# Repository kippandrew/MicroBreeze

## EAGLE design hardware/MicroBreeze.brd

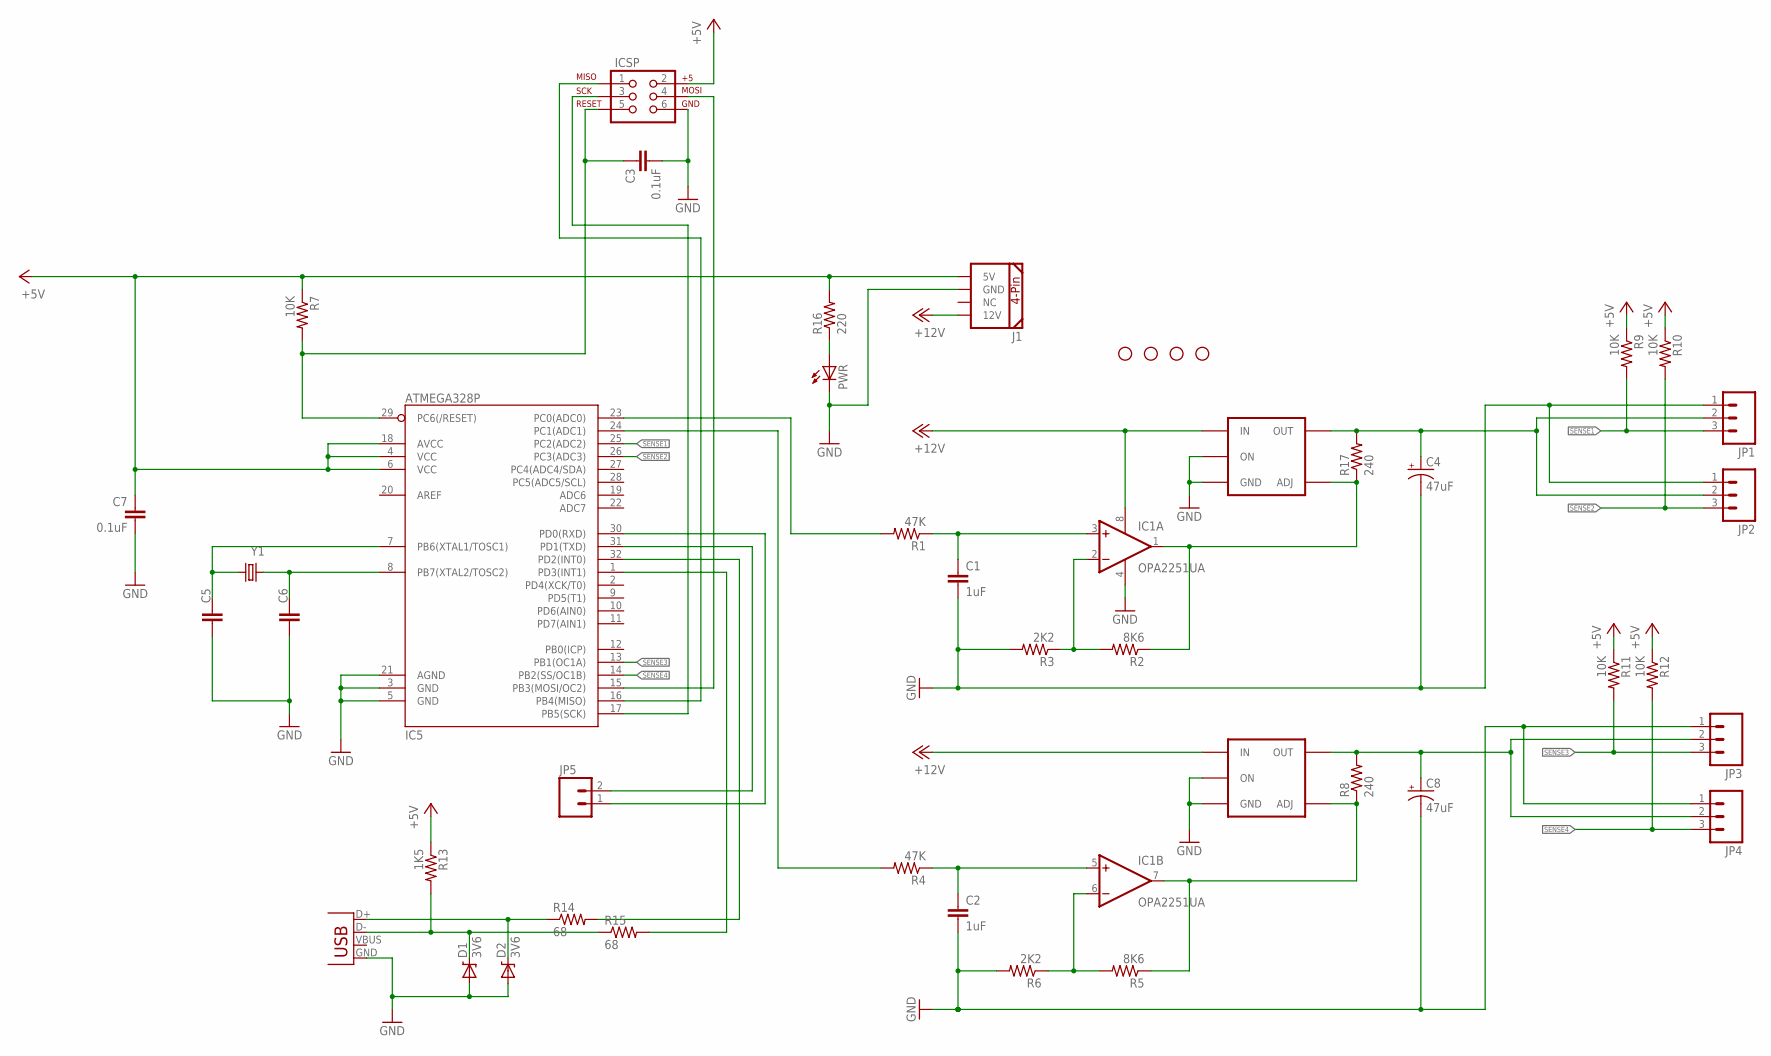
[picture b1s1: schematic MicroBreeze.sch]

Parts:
C1, C2: 1uF; 0805
C3, C7: 0.1uF; 0805
C4, C8: 47uF; EIA3528
C5, C6: .22uF; 0805
D1, D2: 3V6; SOD-323
HOLE1, HOLE2, HOLE3, HOLE4: STAND-OFF
IC1: OPA2251UA; SO08
IC3, IC4: LM2941TO220-V; TO220-51
IC5: ATMEGA328P; TQFP32-08
ICSP: AVR_SPI_PRG_6PTH; 2X3
J1: COMPUTER-PERIPHERAL-POWERVERTICAL; COMPUTER-PERIPHERAL-POWER
JP1, JP2, JP3, JP4: M03POLAR; MOLEX-1X3
JP5: M02PTH; 1X02
PWR: LED1206; LED-1206
R1, R4: 47K; 0805
R2, R5: 8K6; 0805
R3, R6: 2K2; 0805
R7, R9, R10, R11, R12: 10K; 0805
R8, R17: 240; 0805
R13: 1K5; 0805
R14, R15: 68; 0805
R16: 220; 0805
USB: USB-A-SMD; USB-A-S-NOSILK-FEMALE
Y1: 16MHZ; HC49US

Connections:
+5V: C7.1, IC5.4 (VCC), IC5.6 (VCC), IC5.18 (AVCC), ICSP.2, J1.5V, R7.1, R9.1, R10.1, R11.1, R12.1, R13.1, R16.2
+12V: IC1.8 (V+), IC3.4 (IN), IC4.4 (IN), J1.12V
D+: D2.1 (C), R14.1, USB.D+
D-: D1.1 (C), R13.2, R15.1, USB.D-
GND: C1.2, C2.2, C3.2, C4.C (-), C5.2, C6.2, C7.2, C8.C (-), D1.2 (A), D2.2 (A), IC1.4 (V-), IC3.2 (ON), IC3.3 (GND), IC4.2 (ON), IC4.3 (GND), IC5.3 (GND), IC5.5 (GND), IC5.21 (AGND), ICSP.6, J1.GND, JP1.1, JP2.1, JP3.1, JP4.1, PWR.C, R3.2, R6.2, USB.GND
unnamed: IC5.30 (PD0(RXD)), JP5.1
unnamed: IC1.1 (OUT), IC3.1 (ADJ), R2.1, R17.1
unnamed: IC5.16 (PB4(MISO)), ICSP.1
unnamed: IC5.31 (PD1(TXD)), JP5.2
unnamed: IC5.23 (PC0(ADC0)), R1.2
unnamed: C5.1, IC5.7 (PB6(XTAL1/TOSC1)), Y1.2
unnamed: PWR.A, R16.1
unnamed: C4.A (+), IC3.5 (OUT), JP1.2, JP2.2, R17.2
unnamed: C6.1, IC5.8 (PB7(XTAL2/TOSC2)), Y1.1
unnamed: IC5.17 (PB5(SCK)), ICSP.3
unnamed: IC5.15 (PB3(MOSI/OC2)), ICSP.4
unnamed: IC5.24 (PC1(ADC1)), R4.2
unnamed: C8.A (+), IC4.5 (OUT), JP3.2, JP4.2, R8.2
unnamed: C1.1, IC1.3 (+IN), R1.1
unnamed: IC1.2 (-IN), R2.2, R3.1
unnamed: C2.1, IC1.5 (+IN), R4.1
unnamed: IC1.6 (-IN), R5.2, R6.1
unnamed: IC1.7 (OUT), IC4.1 (ADJ), R5.1, R8.1
unnamed: IC5.32 (PD2(INT0)), R14.2
unnamed: IC5.1 (PD3(INT1)), R15.2
RESET: C3.1, IC5.29 (PC6(/RESET)), ICSP.5, R7.2
SENSE1: IC5.25 (PC2(ADC2)), JP1.3, R9.2
SENSE2: IC5.26 (PC3(ADC3)), JP2.3, R10.2
SENSE3: IC5.13 (PB1(OC1A)), JP3.3, R11.2
SENSE4: IC5.14 (PB2(SS/OC1B)), JP4.3, R12.2

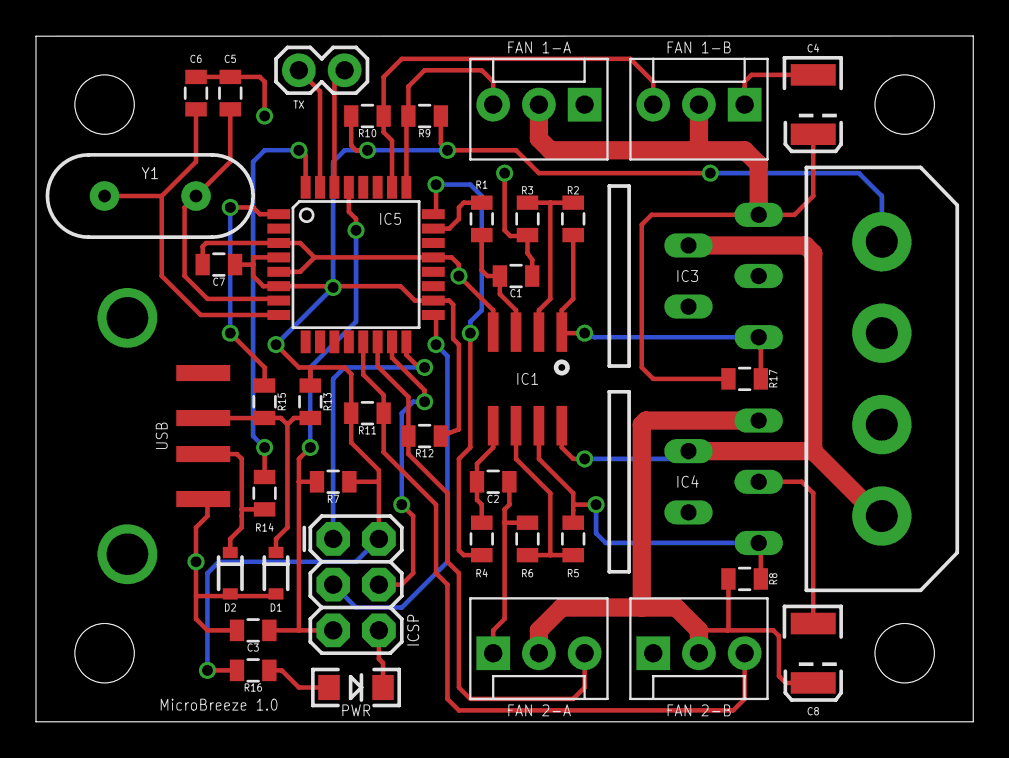
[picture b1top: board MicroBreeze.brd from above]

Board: 2 copper layers, 52.1 x 38.1 mm, 45 parts (0 on the bottom side), 30 nets.

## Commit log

2014-11-15 Update board
2014-11-18 More work on board
2014-11-19 Updated board with LM2341
2014-11-20 Add filter caps
2014-11-20 Board updates

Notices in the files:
parts and their libraries:
SparkFun-Connectors: Licensing: Creative Commons ShareAlike 4.0 International - https://creativecommons.org/licenses/by-sa/4.0
SparkFun: Licensing: CC v3.0 Share-Alike You are welcome to use this library for commercial purposes.
